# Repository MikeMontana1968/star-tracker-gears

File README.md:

# Sidereal star tracker

A standalone device that turns a camera at one revolution per **sidereal day**
(86164.0905 s) for wide-field astrophotography. It wakes at dusk, configures and
starts a GoPro HERO6 night lapse, tracks until dawn, stops the camera, and
rewinds ready for the next night.

---

> **Picking this up again?** Read **[RESUME.md](RESUME.md)** first. The
> controller PCB (Rev C, for the 30-pin ESP32 in hand) is generated, clean
> in ERC and DRC, and ready to order.
>
> **Building it?** The illustrated assembly guide is
> [docs/assembly_guide/stjarnspar.html](docs/assembly_guide/stjarnspar.html):
> gearbox, board, smoke test, wiring, first power-up, use, and the schematics.
> Rebuild it with `python docs/assembly_guide/build.py` (needs Fritzing 1.0.8
> and KiCad 10). The Fritzing wiring project is
> [hardware/fritzing/star_tracker_wiring.fzz](hardware/fritzing/star_tracker_wiring.fzz),
> generated by `gen_fritzing.py` from the KiCad layout.

## Where this stands

| Area | State |
|---|---|
| Gearbox design | **Settled.** 2048:1, verified in CAD, every STL manifold |
| Printer calibration | **Measured.** Post/hole offset 0.50 mm; motor pinion bore pending one test print |
| Backlash | **Validated** on a test pair at 0.25 mm. One drag spot traced to the pinion — reprint with Z Seam = Random |
| Baseplate | **Ordered** from SendCutSend, 4.3 mm 6061 |
| Output shaft + encoder | **Designed**, needs the bearing gauge printed before the tower |
| Electronics | **PCB Rev C** ([hardware/PCB.md](hardware/PCB.md)) — 150 x 100 mm, all through-hole, every module socketed, generated from source; laid out for the 30-pin ESP32 after the pin check. ERC/DRC clean, not yet fabricated |
| Firmware | **Architecture settled** ([FIRMWARE.md](FIRMWARE.md)); nothing written beyond the timing core |
| Under the sky | Not yet |

**Next three things**, in order:

1. Print `_scratch/BEARINGGAUGE_pockets.stl`, set `$BrgFit`, then print the tower.
2. Print `pinion.stl` + the two bore variants next to `stage.stl`; keep the one
   that slides onto the NEMA17 shaft without force.
3. Build the polar wedge. **Before** the gearbox — see §2 below.

---

## The train

```
NEMA17 --15T--> [120T|15T] --> [120T|15T] --> [120T|24T] --> 96T --> camera
   module 1.0       8:1            8:1            8:1        4:1
                                                        module 2.0
```

**8 × 8 × 8 × 4 = 2048 : 1**

| | |
|---|---|
| microsteps / sidereal day | 13,107,200 (200 steps × 1/32 × 2048) |
| step interval | 6573.80 µs |
| step rate | 152.13 steps/s |
| motor speed | 1.426 rpm |
| output resolution | 0.099 arcsec/µstep |
| centre distances | 67.5 / 67.5 / 67.5 / 120.0 mm |
| gear stack | 226.5 × 279 mm envelope, 24.5 mm tall |
| baseplate | 121.5 × 174 × 4.3 mm, ~182 g |

---

## The two things that actually matter

Everything else in this project falls out of these.

### 1. Only the final pinion's radius sets short-exposure trailing

For any mesh, both gears contribute equally to output error per unit
eccentricity — the pinion's smaller radius exactly cancels its higher reduction.
But their *periods* differ, and trailing depends on how much the error moves
**during** an exposure:

```
excursion over exposure t  =  (e / r_pinion) × 2π t / 86164
```

Only `r_pinion` survives. That one equation drove the redesign from 4608:1 to
2048:1: a module-2 24-tooth final pinion (r = 24 mm) instead of module-1 15-tooth
(r = 7.5 mm) cuts a 0.1 mm eccentricity from ~60 arcsec to ~19 arcsec on every
300 s sub. Stages 1–3 divide by 2048, 256 and 32 — they can be as sloppy as the
printer likes.

### 2. Polar alignment dominates all of it

```
1° of misalignment  →  ~16 arcsec/min of drift
```

That swamps every mechanical error above. A sight tube down the RA axis getting
you to 0.25° is worth more than any amount of gear precision. **Build the wedge
first.**

Derivations, rejected alternatives and the design history are in
**[DESIGN_NOTES.md](DESIGN_NOTES.md)**.

---

## Layout

Square fold, 90° at each stage. Shaft centres in mm:

| Shaft | x | y | Carries |
|---|---|---|---|
| 0 motor | 0 | 0 | 15T module-1 pinion |
| 1 | 67.5 | 0 | 120T + 15T |
| 2 | 67.5 | 67.5 | 120T + 15T |
| 3 | 0 | 67.5 | 120T + **24T module-2** |
| 4 output | 0 | −52.5 | 96T module-2, 196 mm OD, on bearings |

**Constraints this layout imposes** — all three were found by drawing it to scale:

- **Nothing over Ø13 mm inline at shafts 0–3.** Tightest radial clearance is
  `67.5 − 61 − 2.5 = 4.0 mm`, shaft to neighbouring wheel tip. A 625ZZ (16 mm)
  gives −1.5 mm and collides; a Ø10 spacer leaves 1.5 mm. **Never fit a stock
  5 mm shaft collar at shafts 2 or 3.**
- **Shafts 0 and 1 must stay below 19 mm.** The output wheel sits over both. A
  stock NEMA17 shaft is 24 mm and fouls it — trim to ~10 mm above the plate.
- **No top plate on shafts 0 and 1**, same reason. Cantilever them; their errors
  divide by 2048 and 256, so it costs nothing.

**Every mesh needs its own Z band.** `pinion_tip + wheel_tip = a + 2m` always, so
a pinion collides with any adjacent wheel, mating or not. Four meshes, four
bands, irreducible. Band *height* can shrink (3 mm faces take the stack from
24.5 to 16 mm) but band *count* cannot.

---

## Baseplate

121.5 × 174 × **4.3 mm** 6061 aluminium, ~182 g (4.3 was the nearest stock to
the 4.0 designed). Cut, not printed — too big for the bed, and it wants
stiffness rather than strength.

Thickness is dimensionally free here: **all gear heights reference the plate's
top face**, so it lives below the datum. It only moves fastener lengths.

The outline is a hull of lobes at the five shaft centres, **not** a slab under
the whole gear footprint: the wheels overhang on purpose, so the plate only
carries the shafts and the motor. That is what takes it from ~740 g to 170 g.

The wedge/tripod interface is **4 × M5 on Ø50 centred on the output axis**, not
on the plate centroid. The camera moment gets reacted where it is generated, and
that short load path is why 4 mm is enough.

- `out/docs/baseplate_cut.dxf` — **send this**, 4 ARC + 4 LINE + 16 CIRCLE.
  State **mm** on upload; R12 DXF has no reliable units record
- `out/docs/baseplate_cut.svg` — same geometry as SVG, 17 closed contours
- `out/docs/baseplate_template.pdf` — 1:1 on US Letter, two scale bars
- `out/docs/baseplate_assembly_guide.pdf` — bench reference: component outlines,
  spacer heights, fastener sizes. **Not to scale**, by necessity — the gear
  footprint is 226 × 279 mm

`baseplate_geom.py` is the single source for all three, so they cannot drift.
Never export DXF from OpenSCAD — it emits 708 loose LINE segments and no
circles at all.

---

## Output shaft and AS5600 encoder

The output is the one shaft that rotates. The encoder magnet must sit on the axis
and turn with the wheel, and the camera load wants real bearings anyway.

Printed tower halves, hubs, washer, cap and bracket, plus a 5 mm ground shaft
**cut to 55 mm**, 2 × 625ZZ, a **diametric** 6 × 2.5 magnet and an AS5600
breakout. Verified: **magnet face to die = 2.0 mm**, inside the sensor's
0.5–3.0 mm window; bearing centres 30 mm apart.

Three design points worth not undoing:

- **The tower halves clamp the baseplate between them** (Rev B). Rev A's cone
  under the flange sat inside the plate. See PRINTING.md.

- **The wheel locates on a Ø22 register** on the lower hub and is clamped by six
  M3 — not centred by its own bore. A printed 5.2 bore on a 5 mm shaft is worth
  ~0.2 mm of eccentricity, which is exactly what §1 says to avoid.
- **The sensor bracket registers on the same tower boss that holds the lower
  bearing, and stops against the tower's clamp disc.** The AS5600 needs the
  magnet centred within ~0.25 mm and gapped at 2.0 mm; both come from printed
  features rather than from careful assembly.

Firmware aid: the AS5600's `AGC` and `MAGNITUDE` registers report "too far / too
close" as a number, so the air gap is measured, not guessed.

---

## Scheduled operation

Full architecture, cycle diagram, BOM and pin map: **[HARDWARE.md](HARDWARE.md)**.

- **ESP32, not a Pi.** Unattended robustness: a flat battery mid-write corrupts
  an SD card, LittleFS comes back. Also ~0.6 W cheaper, ≈7 Wh a night.
- **GoPro over WiFi, not BLE.** The documented GoPro BLE API starts at HERO9 —
  the earlier HERO5 Bluetooth failure was expected, not a Pi problem. HERO6 uses
  the `gpControl` HTTP API at 10.5.5.9, woken by a magic packet.
- **Captive web UI on the ESP32's own AP.** No app, no pairing. One radio means
  one mode at a time, which keeps the state machine simple.
- **~43 Wh per night, 69% of it the camera.** Three nights unaided needs 130 Wh;
  a 6 Ah pack plus a 20 W panel is lighter and never runs out.

**Two cycle rules that are not obvious:** always approach the start angle from
the forward direction (rewind reverses ~750 arcsec of backlash, which otherwise
gets taken up as drift during your first subs), and bias the counterweight so the
mesh stays loaded on one flank.

### Why there is no speed feedback loop

A stepper is synchronous, and the ESP32 crystal is ±20 ppm — over a 300 s exposure
that is 0.000025° at the output. There is nothing for a speed loop to correct. Use
StallGuard for *stall detection*, which is a real failure mode.

What must be exact is the step interval: 6573.80 µs is not an integer, and
rounding costs ~5 s/day of drift. `sidereal_drive.ino` carries the remainder in a
64-bit accumulator, so the rate is exact for **any** ratio — which is what freed
the design to choose gears for mechanical convenience.

---

## Printer calibration — measured, not guessed

These live at the top of `build.ps1`. They are the hardest-won numbers here.

| Constant | Value | How it was found |
|---|---|---|
| `$Bore` | 6.00 | gears run on #12 screws (5.49 mm), was 5.20 for nails |
| `$MotorBore` | 5.45 | NEMA17's ground 5.00 mm shaft needs its own bore |
| `$PostD` | 4.70 | fit gauge |
| `$BrgFit` | 0.50 | **provisional** — print the bearing gauge |

**A printed post must run ~0.50 mm under a printed hole's nominal diameter** for
a snug rotating fit on this printer. That is hole shrink plus post growth
combined, and it is on the high side of typical (0.30–0.40), which hints flow
runs a few percent hot.

Three gauges exist because these cannot be predicted, only measured:
`FITGAUGE` (posts), `BOREGAUGE` (holes), `BEARINGGAUGE` (625ZZ pockets).

---

## Repo layout

```
star_tracker_gears.scad     the model — single source for every part
make_baseplate_pdf.py       1:1 drilling template (reportlab)
build.ps1                   regenerates every artifact
firmware/sidereal_drive/    ESP32 sketch
PRINTING.md                 what to print, in what order, with what settings
DESIGN_NOTES.md             why the gearbox is what it is
HARDWARE.md                 electronics architecture, BOM
FIRMWARE.md                 firmware architecture, pin map, build order — START HERE for code
hardware/                   the controller PCB, generated from Python
  PCB.md                    board design notes, jumpers, assembly order
  design.py                 netlist + values + the ESP32/TMC pin maps
  place.py                  floorplan; layout.py packer; route.py maze router
  star_tracker_ctrl/        the generated KiCad project
out/                        generated — meshes gitignored
  docs/                     renders, laser SVG, baseplate SVG, template
  _scratch/                 calibration gauges, test jig, superseded exports
```

## Building

```powershell
.\build.ps1                     # everything
.\build.ps1 -Group gears        # the parts you print
.\build.ps1 -Group encoder      # output shaft assembly
.\build.ps1 -Group calibration  # the three gauges
.\build.ps1 -Group docs         # renders, SVGs, PDF
.\build.ps1 -List               # show targets without building
```

Needs OpenSCAD 2021.01+ and Python with `reportlab`. Every STL target is checked
for `Simple: yes` and the build fails if one is not.

---

## Traps worth remembering

Each of these cost real time and none of them announce themselves.

- **OpenSCAD: `children()` nested inside `union()` inside `difference()` inside
  `if()` does not resolve.** The section cut silently did nothing. Apply cuts at
  the call site instead.
- **OpenSCAD preview mis-renders `difference()` when children carry `color()`.**
  Geometry was correct all along; only the OpenCSG preview lied. Section images
  need `--render`, which then discards colour — hence the exploded view.
- **PowerShell 5.1 strips inner quotes** from native-exe arguments, so
  `part="spacers"` arrives as a bare variable. Backslash-escape them. And `2>&1`
  on a native command wraps stderr in ErrorRecords that abort under
  `$ErrorActionPreference = 'Stop'`.
- **A part can be un-printable in every orientation.** The bearing tower had a
  166 mm2 first layer one way up and an 8 mm 90° ledge the other. Splitting it
  fixed the printing. Check bed contact area, not just overhang angle.
- **Check a printable part against its neighbours, not just the bed.** Rev A's
  split added a cone for printability that sat inside the aluminium plate. It
  was found by drawing the assembly guide, not by the build. Rev B puts the
  plate between the halves, so each prints plate-face-down and only narrows
  going up.
- **Verify meshes, not file sizes.** Bounding-box checks caught a wheel that had
  changed only in float formatting, and a D-shaft cut that had sliced the pinion
  into five disconnected bodies (`Volumes: 5` instead of 2).
- **Binaries need `.gitattributes`.** Without it a fresh Windows clone rewrites
  LF to CRLF *inside* the PDF and PNGs and corrupts them.

## Order of work

1. Calibration gauges, then the test pair. Tune `backlash`.
2. **Build the polar wedge before the gearbox.**
3. Open-loop drive, 50 mm lens, one 5-minute sub. **Measure the trailing.**
4. Only then decide what to fix. Adding an encoder before you have data is
   solving an imaginary problem — the encoder in this design is for *scheduling*
   and stall detection, not for correcting tracking.

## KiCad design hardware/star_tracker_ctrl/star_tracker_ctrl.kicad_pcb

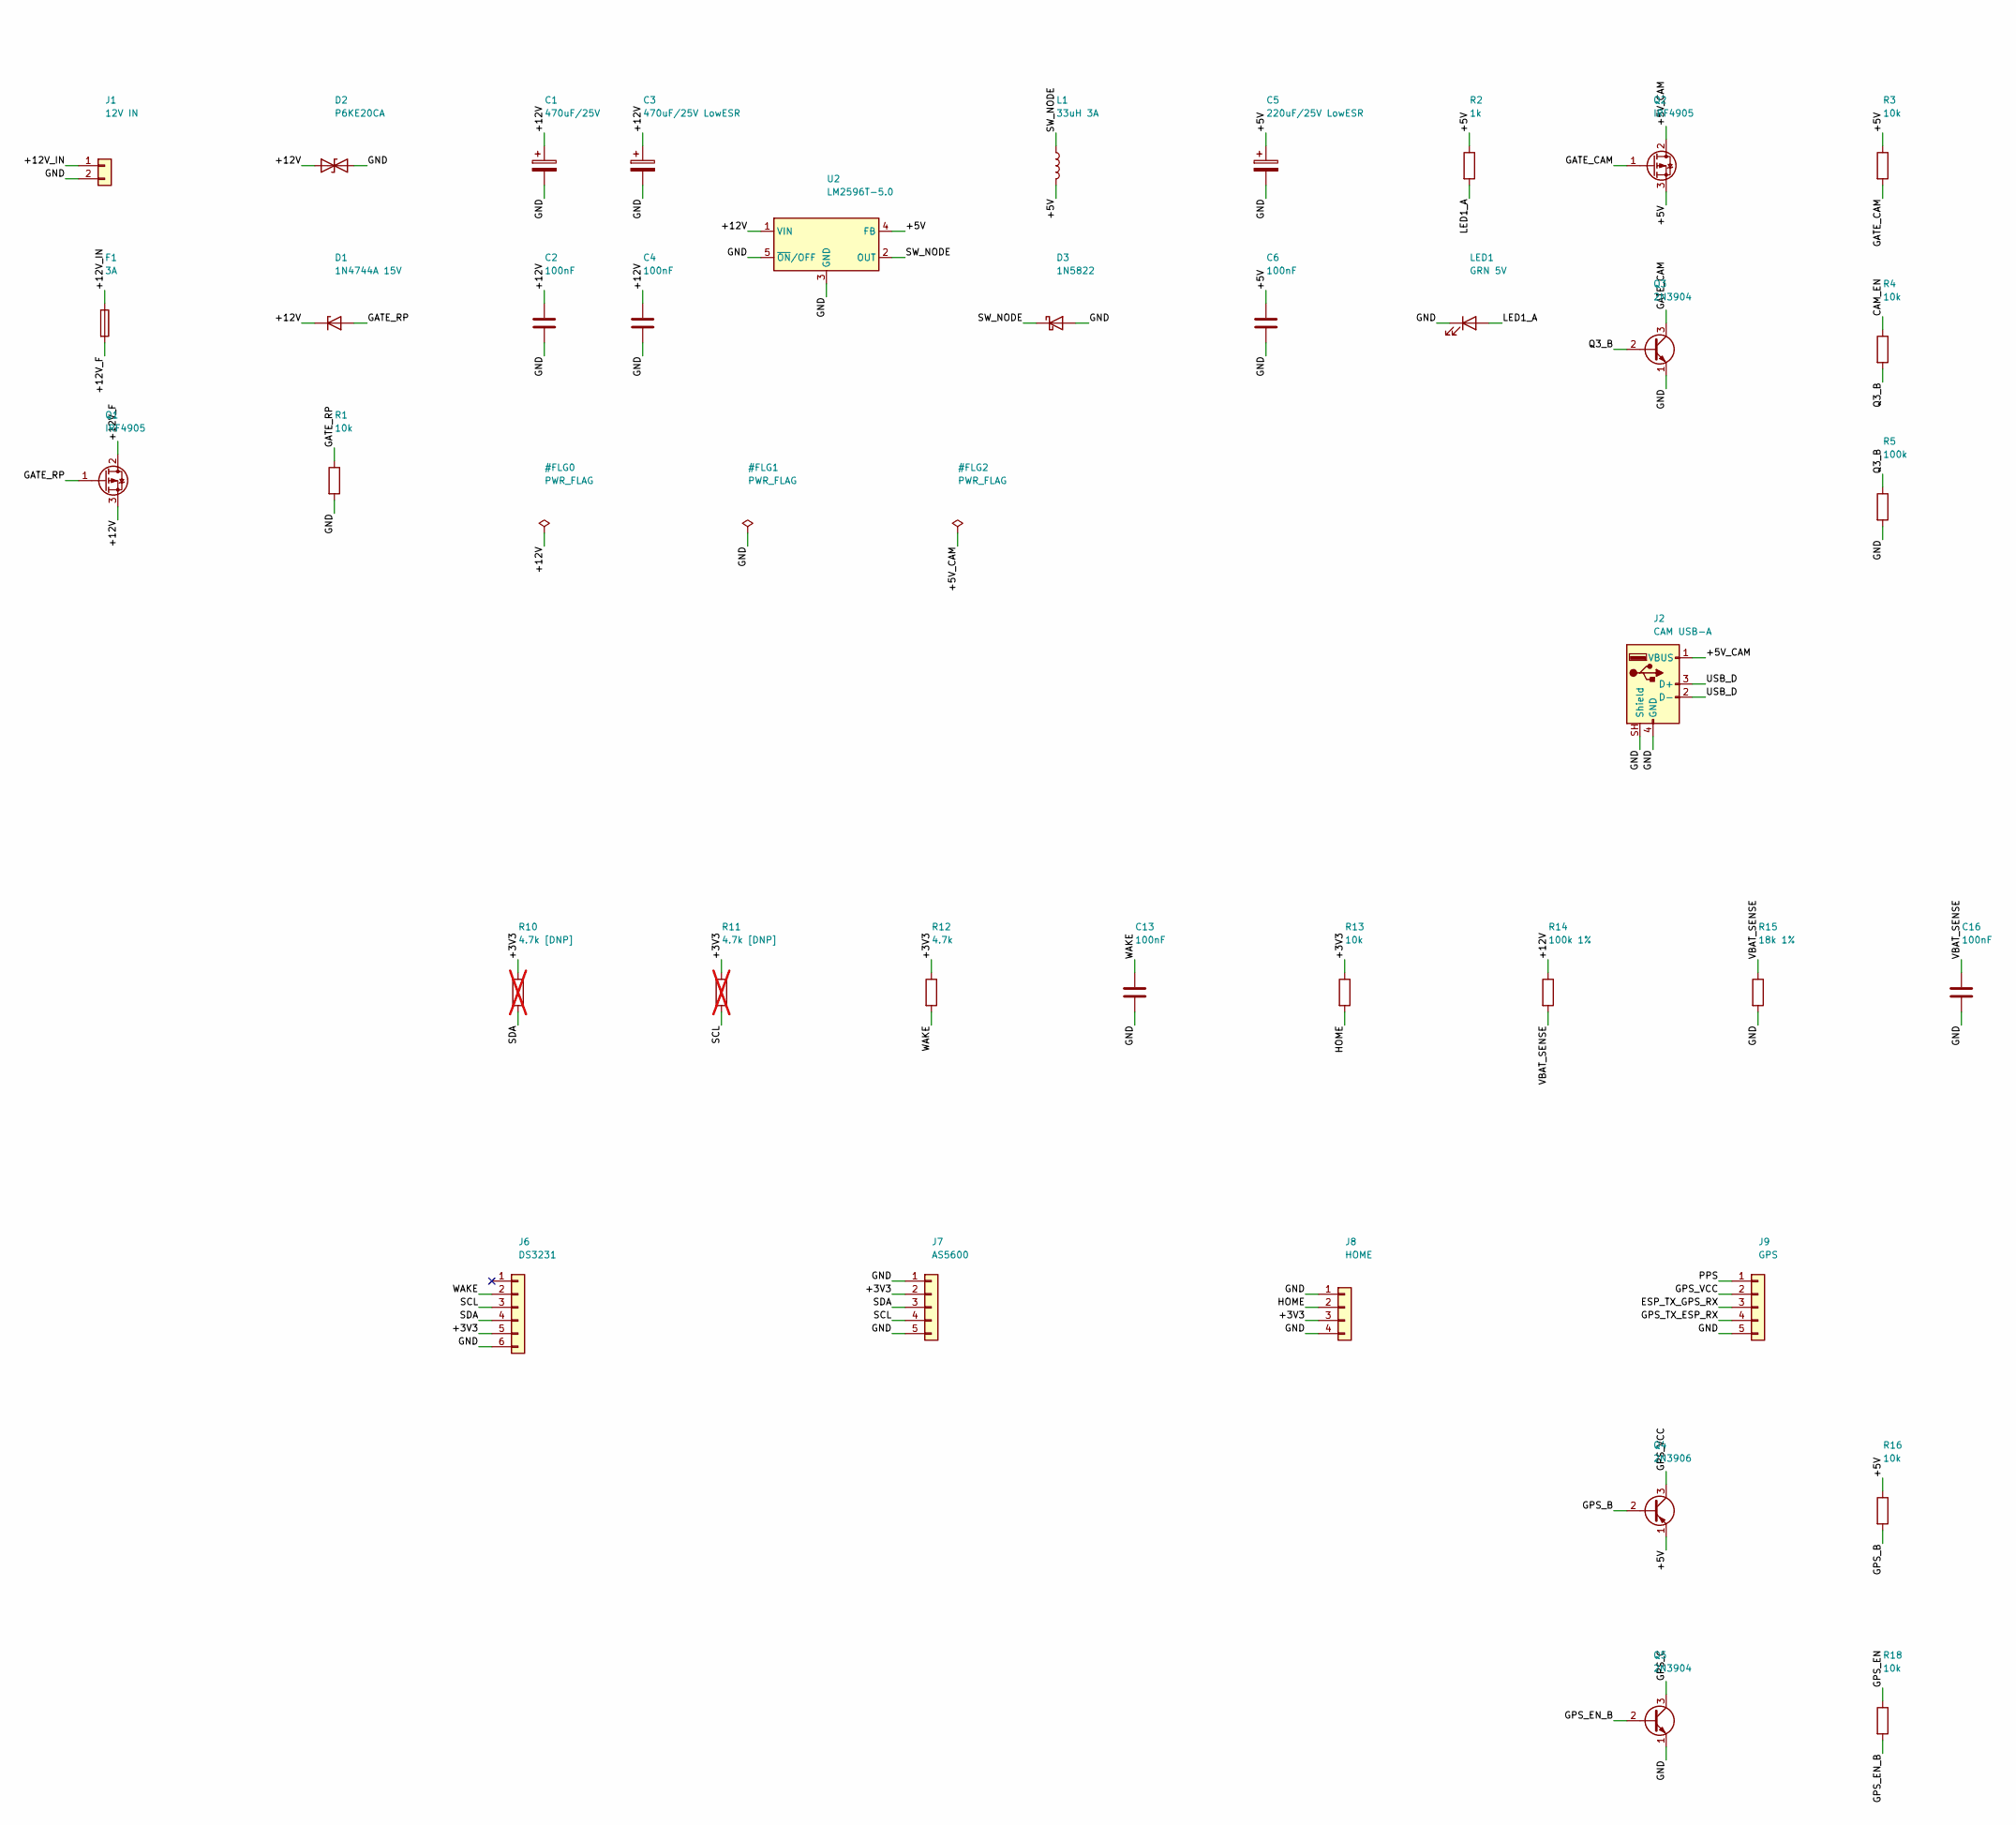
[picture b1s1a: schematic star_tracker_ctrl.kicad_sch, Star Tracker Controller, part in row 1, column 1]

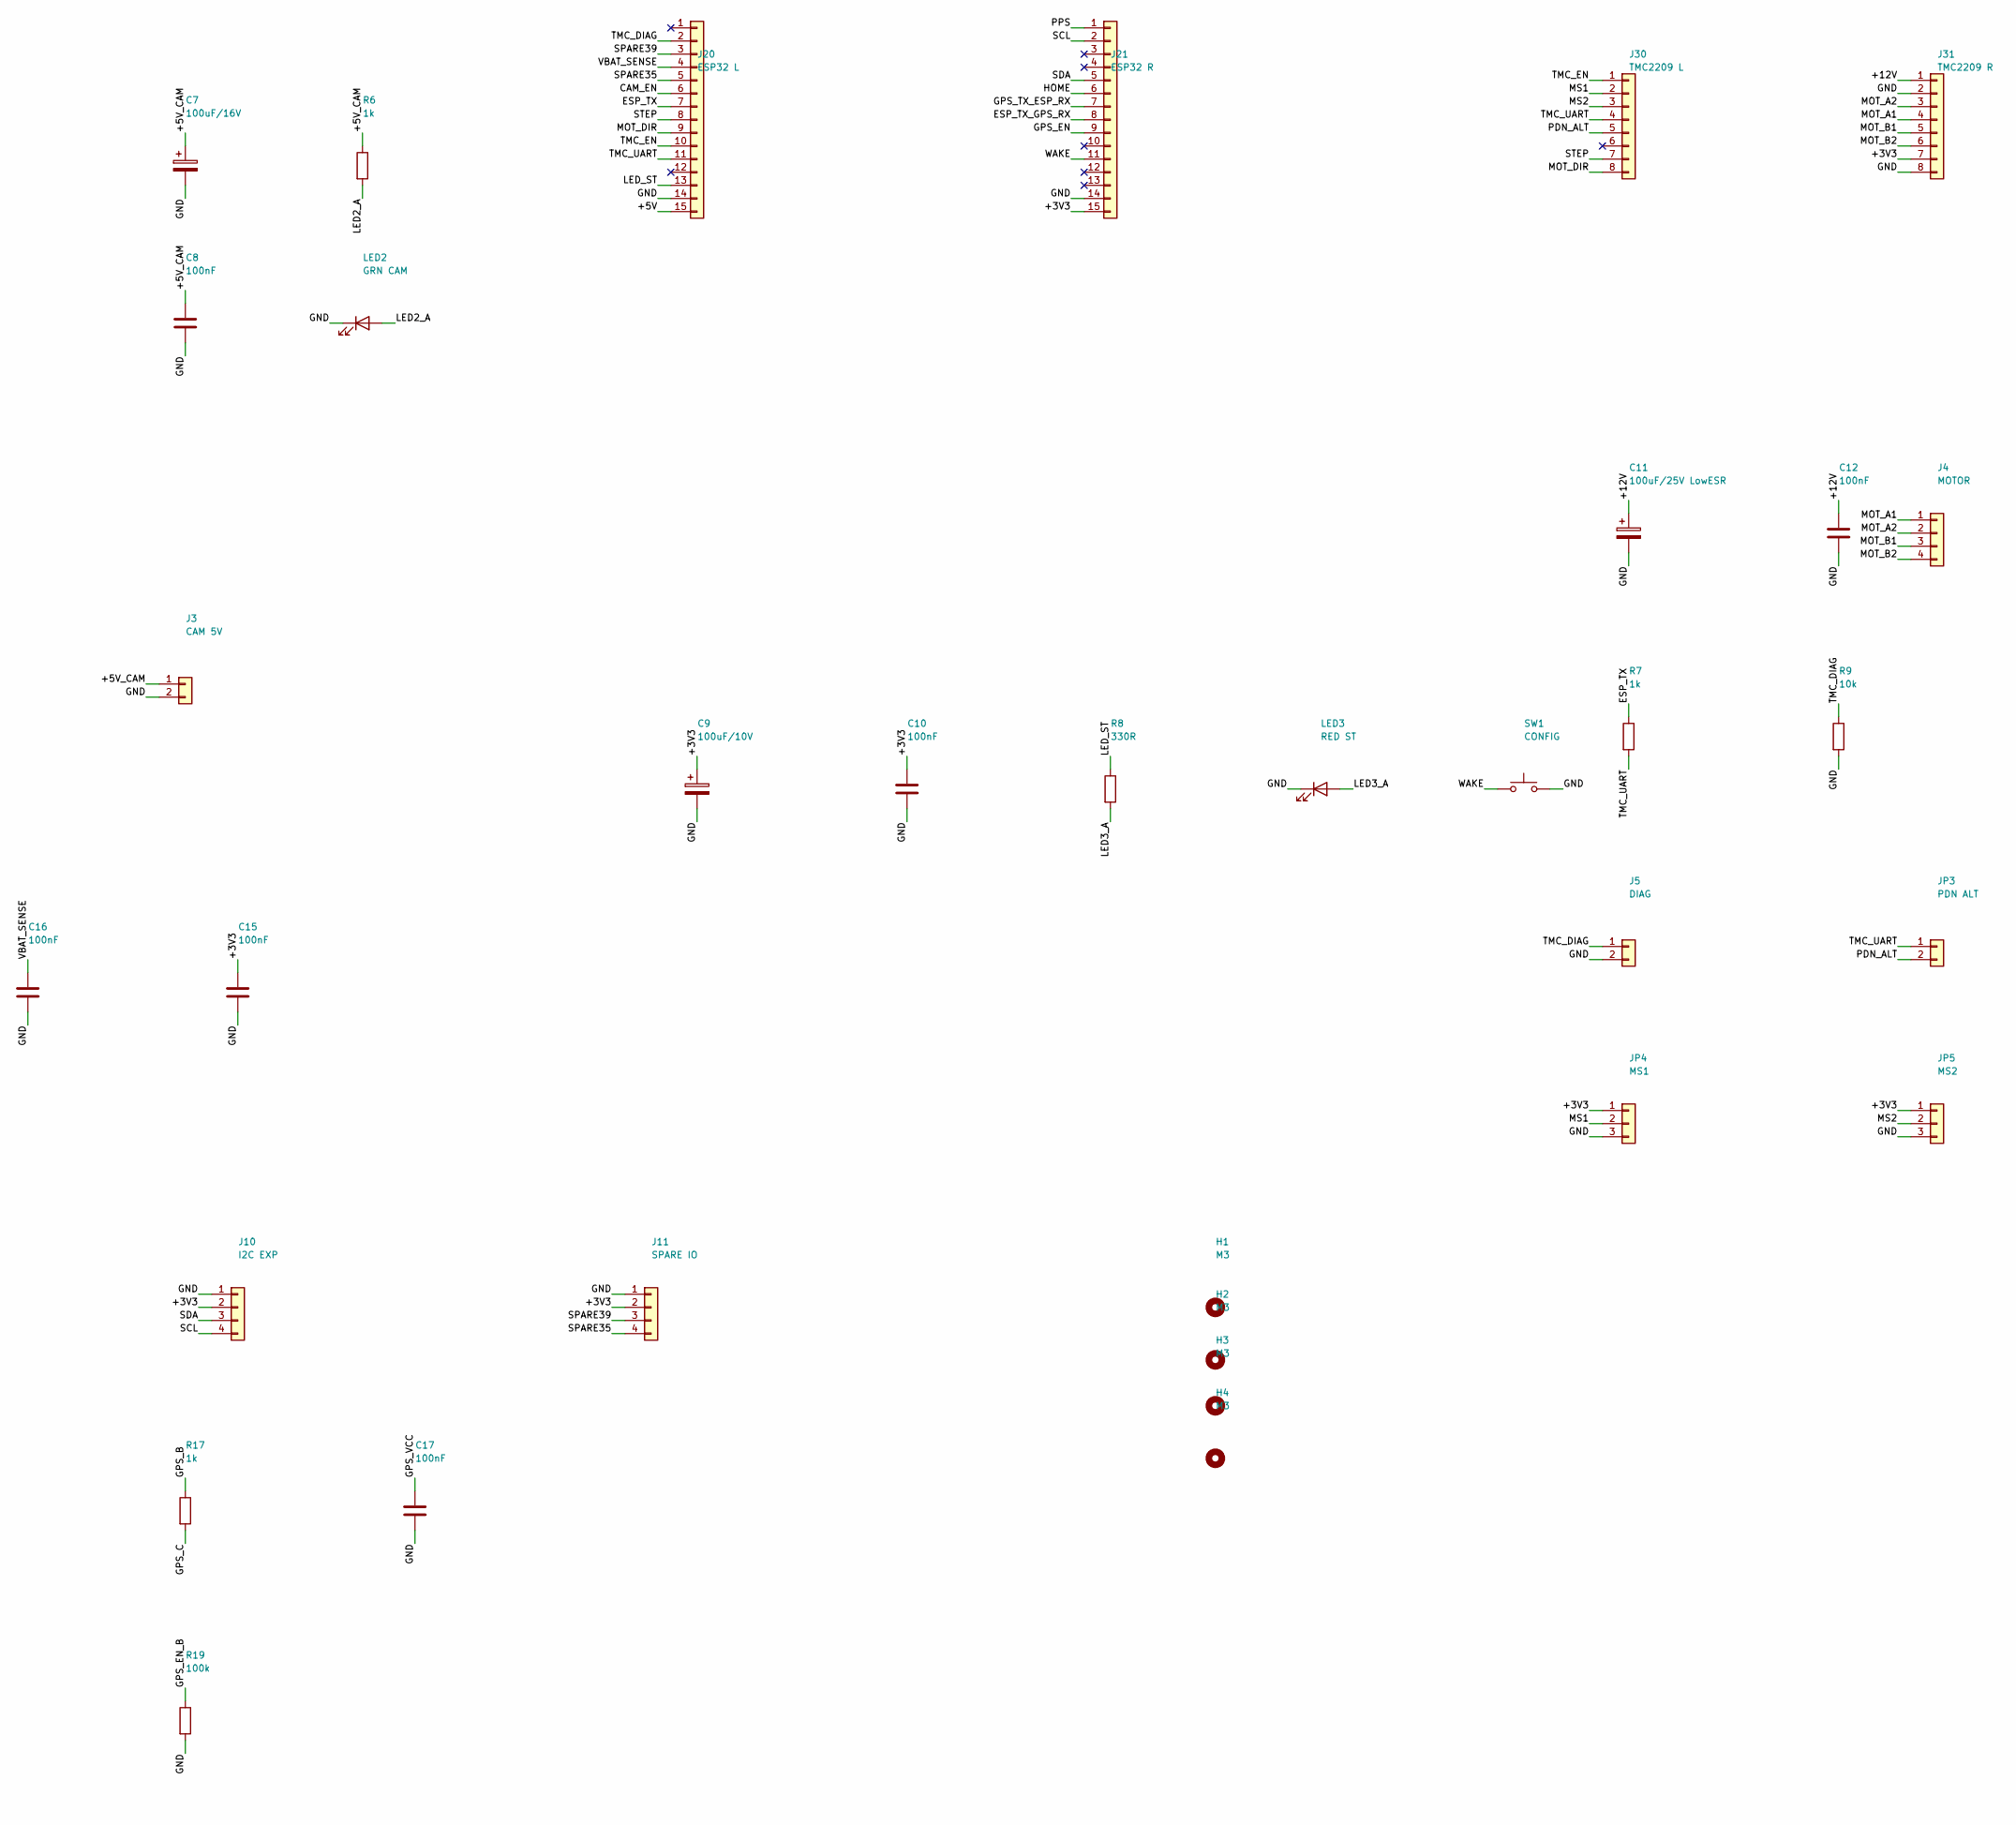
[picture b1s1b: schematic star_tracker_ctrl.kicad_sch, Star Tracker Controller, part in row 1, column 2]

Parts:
C1: 470uF/25V; CP_Radial_D10.0mm_P5.00mm
C2, C4, C6, C8, C10, C12, C13, C15, C16, C17: 100nF; C_Disc_D5.0mm_W2.5mm_P2.50mm
C3: 470uF/25V LowESR; CP_Radial_D10.0mm_P5.00mm
C5: 220uF/25V LowESR; CP_Radial_D10.0mm_P5.00mm
C7: 100uF/16V; CP_Radial_D8.0mm_P3.50mm
C9: 100uF/10V; CP_Radial_D8.0mm_P3.50mm
C11: 100uF/25V LowESR; CP_Radial_D10.0mm_P5.00mm
D1: 1N4744A 15V; D_DO-41_SOD81_P2.54mm_Vertical_CathodeUp
D2: P6KE20CA; D_DO-15_P3.81mm_Vertical_AnodeUp
D3: 1N5822; D_DO-201AD_P5.08mm_Vertical_CathodeUp
F1: 3A; Fuseholder_Clip-5x20mm_Littelfuse_111_Inline_P20.00x5.00mm_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
H1, H2, H3, H4: M3; MountingHole_3.2mm_M3
J1: 12V IN; TerminalBlock_MaiXu_MX126-5.0-02P_1x02_P5.00mm
J2: CAM USB-A; USB_A_Wuerth_614004134726_Horizontal
J3: CAM 5V; TerminalBlock_MaiXu_MX126-5.0-02P_1x02_P5.00mm
J4: MOTOR; TerminalBlock_MaiXu_MX126-5.0-04P_1x04_P5.00mm
J5: DIAG; PinHeader_1x02_P2.54mm_Vertical
J6: DS3231; PinSocket_1x06_P2.54mm_Vertical
J7: AS5600; PinHeader_1x05_P2.54mm_Vertical
J8: HOME; PinHeader_1x04_P2.54mm_Vertical
J9: GPS; PinHeader_1x05_P2.54mm_Vertical
J10: I2C EXP; PinHeader_1x04_P2.54mm_Vertical
J11: SPARE IO; PinHeader_1x04_P2.54mm_Vertical
J20: ESP32 L; PinSocket_1x15_P2.54mm_Vertical
J21: ESP32 R; PinSocket_1x15_P2.54mm_Vertical
J30: TMC2209 L; PinSocket_1x08_P2.54mm_Vertical
J31: TMC2209 R; PinSocket_1x08_P2.54mm_Vertical
JP3: PDN ALT; PinHeader_1x02_P2.54mm_Vertical
JP4: MS1; PinHeader_1x03_P2.54mm_Vertical
JP5: MS2; PinHeader_1x03_P2.54mm_Vertical
L1: 33uH 3A; L_Radial_D12.0mm_P5.00mm_Fastron_11P
LED1: GRN 5V; LED_D3.0mm
LED2: GRN CAM; LED_D3.0mm
LED3: RED ST; LED_D3.0mm
Q1, Q2: IRF4905; TO-220-3_Vertical
Q3, Q5: 2N3904; TO-92_Inline_Wide
Q4: 2N3906; TO-92_Inline_Wide
R1, R3, R4, R9, R13, R16, R18: 10k; R_Axial_DIN0207_L6.3mm_D2.5mm_P2.54mm_Vertical
R2, R6, R7, R17: 1k; R_Axial_DIN0207_L6.3mm_D2.5mm_P2.54mm_Vertical
R5, R19: 100k; R_Axial_DIN0207_L6.3mm_D2.5mm_P2.54mm_Vertical
R8: 330R; R_Axial_DIN0207_L6.3mm_D2.5mm_P2.54mm_Vertical
R10, R11: 4.7k [DNP]; R_Axial_DIN0207_L6.3mm_D2.5mm_P2.54mm_Vertical; not fitted
R12: 4.7k; R_Axial_DIN0207_L6.3mm_D2.5mm_P2.54mm_Vertical
R14: 100k 1%; R_Axial_DIN0207_L6.3mm_D2.5mm_P2.54mm_Vertical
R15: 18k 1%; R_Axial_DIN0207_L6.3mm_D2.5mm_P2.54mm_Vertical
SW1: CONFIG; SW_PUSH_6mm
U2: LM2596T-5.0; TO-220-5_P3.4x3.7mm_StaggerOdd_Lead3.8mm_Vertical

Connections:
+3V3: C9.1, C10.1, C15.1, J6.5, J7.2, J8.3, J10.2, J11.2, J21.15, J31.7, JP4.1, JP5.1, R10.1, R11.1, R12.1, R13.1
+5V: C5.1, C6.1, J20.15, L1.2, Q2.3 (S), Q4.1 (E), R2.1, R3.1, R16.1, U2.4 (FB)
+5V_CAM: C7.1, C8.1, J2.1 (VBUS), J3.1, Q2.2 (D), R6.1
+12V: C1.1, C2.1, C3.1, C4.1, C11.1, C12.1, D1.1 (K), D2.1 (A1), J31.1, Q1.3 (S), R14.1, U2.1 (VIN)
+12V_F: F1.2, Q1.2 (D)
+12V_IN: F1.1, J1.1
CAM_EN: J20.6, R4.1
ESP_TX: J20.7, R7.1
ESP_TX_GPS_RX: J9.3, J21.8
GATE_CAM: Q2.1 (G), Q3.3 (C), R3.2
GATE_RP: D1.2 (A), Q1.1 (G), R1.1
GND: C1.2, C2.2, C3.2, C4.2, C5.2, C6.2, C7.2, C8.2, C9.2, C10.2, C11.2, C12.2, C13.2, C15.2, C16.2, C17.2, D2.2 (A2), D3.2 (A), J1.2, J2.4 (GND), J2.SH (Shield), J3.2, J5.2, J6.6, J7.1, J7.5, J8.1, J8.4, J9.5, J10.1, J11.1, J20.14, J21.14, J31.2, J31.8, JP4.3, JP5.3, LED1.1 (K), LED2.1 (K), LED3.1 (K), Q3.1 (E), Q5.1 (E), R1.2, R5.2, R9.2, R15.2, R19.2, SW1.2, U2.3 (GND), U2.5 (~ON/OFF)
GPS_B: Q4.2 (B), R16.2, R17.1
GPS_C: Q5.3 (C), R17.2
GPS_EN: J21.9, R18.1
GPS_EN_B: Q5.2 (B), R18.2, R19.1
GPS_TX_ESP_RX: J9.4, J21.7
GPS_VCC: C17.1, J9.2, Q4.3 (C)
HOME: J8.2, J21.6, R13.2
LED1_A: LED1.2 (A), R2.2
LED2_A: LED2.2 (A), R6.2
LED3_A: LED3.2 (A), R8.2
LED_ST: J20.13, R8.1
MOT_A1: J4.1, J31.4
MOT_A2: J4.2, J31.3
MOT_B1: J4.3, J31.5
MOT_B2: J4.4, J31.6
MOT_DIR: J20.9, J30.8
MS1: J30.2, JP4.2
MS2: J30.3, JP5.2
PDN_ALT: J30.5, JP3.2
PPS: J9.1, J21.1
Q3_B: Q3.2 (B), R4.2, R5.1
SCL: J6.3, J7.4, J10.4, J21.2, R11.2
SDA: J6.4, J7.3, J10.3, J21.5, R10.2
SPARE35: J11.4, J20.5
SPARE39: J11.3, J20.3
STEP: J20.8, J30.7
SW_NODE: D3.1 (K), L1.1, U2.2 (OUT)
TMC_DIAG: J5.1, J20.2, R9.1
TMC_EN: J20.10, J30.1
TMC_UART: J20.11, J30.4, JP3.1, R7.2
USB_D: J2.2 (D-), J2.3 (D+)
VBAT_SENSE: C16.1, J20.4, R14.2, R15.1
WAKE: C13.1, J6.2, J21.11, R12.2, SW1.1

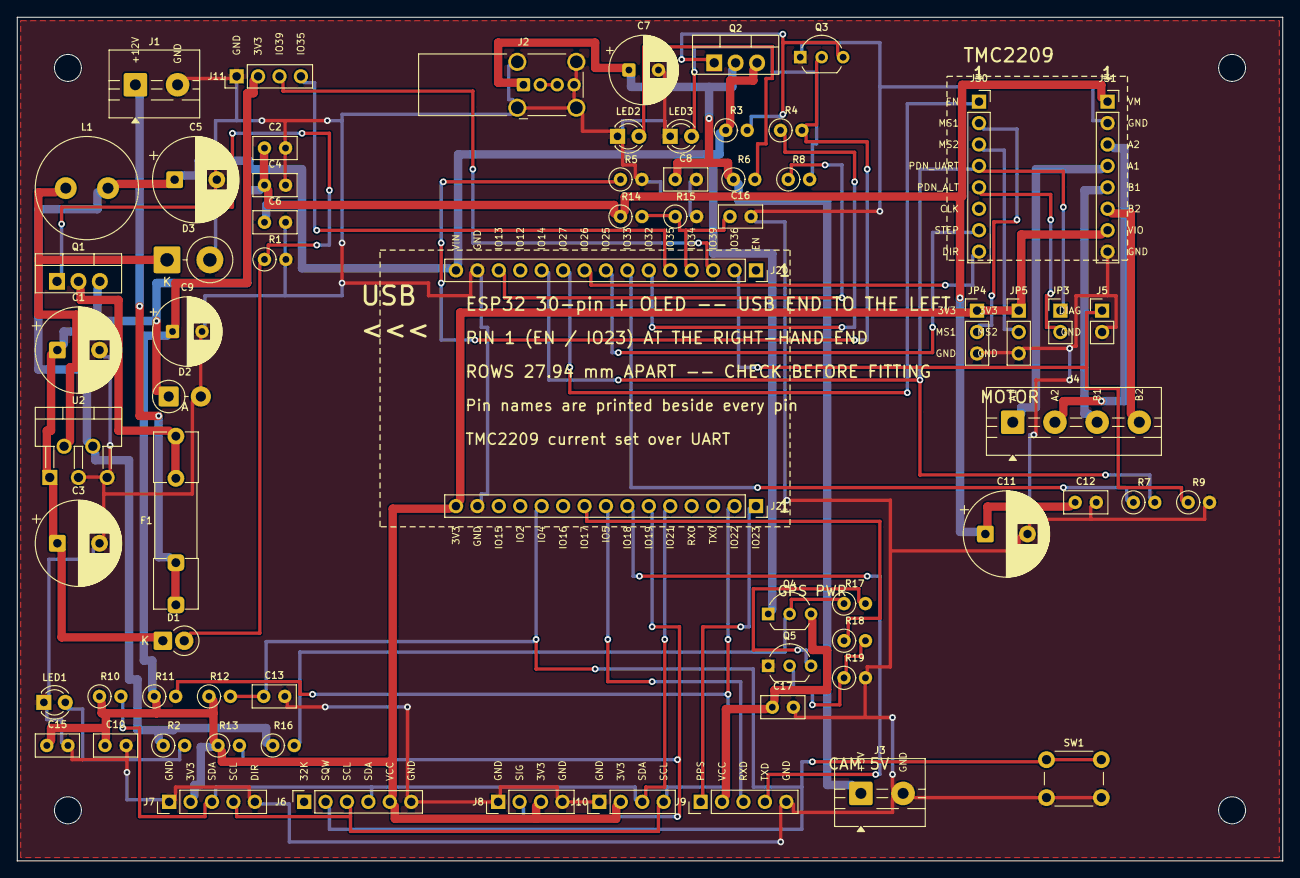
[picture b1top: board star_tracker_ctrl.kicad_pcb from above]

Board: 2 copper layers, 150.0 x 100.0 mm, 72 parts (0 on the bottom side), 45 nets.

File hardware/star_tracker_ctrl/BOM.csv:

Qty,Refs,Value,Footprint,Fitted,Note
1,"C1","470uF/25V","CP_Radial_D10.0mm_P5.00mm",yes,""
1,"C11","100uF/25V LowESR","CP_Radial_D10.0mm_P5.00mm",yes,"VMOT bulk - MUST sit at the driver socket"
10,"C10 C12 C13 C15 C16 C17 C2 C4 C6 C8","100nF","C_Disc_D5.0mm_W2.5mm_P2.50mm",yes,""
1,"C3","470uF/25V LowESR","CP_Radial_D10.0mm_P5.00mm",yes,""
1,"C5","220uF/25V LowESR","CP_Radial_D10.0mm_P5.00mm",yes,""
1,"C7","100uF/16V","CP_Radial_D8.0mm_P3.50mm",yes,""
1,"C9","100uF/10V","CP_Radial_D8.0mm_P3.50mm",yes,""
1,"D1","1N4744A 15V","D_DO-41_SOD81_P2.54mm_Vertical_CathodeUp",yes,"Vgs clamp, cathode to source"
1,"D2","P6KE20CA","D_DO-15_P3.81mm_Vertical_AnodeUp",yes,""
1,"D3","1N5822","D_DO-201AD_P5.08mm_Vertical_CathodeUp",yes,"catch diode, cathode to SW node"
1,"F1","3A","Fuseholder_Clip-5x20mm_Littelfuse_111_Inline_P20.00x5.00mm_D1.05mm_Horizontal",yes,""
1,"J1","12V IN","TerminalBlock_MaiXu_MX126-5.0-02P_1x02_P5.00mm",yes,"12-14.6V LiFePO4 in"
1,"J10","I2C EXP","PinHeader_1x04_P2.54mm_Vertical",yes,"v2 compass"
1,"J11","SPARE IO","PinHeader_1x04_P2.54mm_Vertical",yes,"the upper row's two free pins; both input-only"
1,"J2","CAM USB-A","USB_A_Wuerth_614004134726_Horizontal",yes,"D+/D- shorted = dedicated charging port"
1,"J20","ESP32 L","PinSocket_1x15_P2.54mm_Vertical",yes,""
1,"J21","ESP32 R","PinSocket_1x15_P2.54mm_Vertical",yes,""
1,"J3","CAM 5V","TerminalBlock_MaiXu_MX126-5.0-02P_1x02_P5.00mm",yes,""
1,"J30","TMC2209 L","PinSocket_1x08_P2.54mm_Vertical",yes,""
1,"J31","TMC2209 R","PinSocket_1x08_P2.54mm_Vertical",yes,""
1,"J4","MOTOR","TerminalBlock_MaiXu_MX126-5.0-04P_1x04_P5.00mm",yes,"pins 1-2 one coil, 3-4 the other"
1,"J5","DIAG","PinHeader_1x02_P2.54mm_Vertical",yes,""
1,"J6","DS3231","PinSocket_1x06_P2.54mm_Vertical",yes,"ZS-042 order: 32K SQW SCL SDA VCC GND"
1,"J7","AS5600","PinHeader_1x05_P2.54mm_Vertical",yes,"remote on the encoder bracket; pin5 = DIR->GND"
1,"J8","HOME","PinHeader_1x04_P2.54mm_Vertical",yes,"optional opto flag; GND on BOTH end pins so the pour can always reach one of them"
1,"J9","GPS","PinHeader_1x05_P2.54mm_Vertical",yes,"GY-NEO6MV2: pins 2-5 match its VCC/RX/TX/GND cable; PPS is a flying lead from the module's PPS LED pad"
1,"JP3","PDN ALT","PinHeader_1x02_P2.54mm_Vertical",yes,""
1,"JP4","MS1","PinHeader_1x03_P2.54mm_Vertical",yes,""
1,"JP5","MS2","PinHeader_1x03_P2.54mm_Vertical",yes,""
1,"L1","33uH 3A","L_Radial_D12.0mm_P5.00mm_Fastron_11P",yes,""
1,"LED1","GRN 5V","LED_D3.0mm",yes,""
1,"LED2","GRN CAM","LED_D3.0mm",yes,""
1,"LED3","RED ST","LED_D3.0mm",yes,""
2,"Q1 Q2","IRF4905","TO-220-3_Vertical",yes,"reverse-polarity; drain to source of supply"
2,"Q3 Q5","2N3904","TO-92_Inline_Wide",yes,""
1,"Q4","2N3906","TO-92_Inline_Wide",yes,"PNP high-side switch; the module's own LDO makes 3.3V from this"
7,"R1 R13 R16 R18 R3 R4 R9","10k","R_Axial_DIN0207_L6.3mm_D2.5mm_P2.54mm_Vertical",yes,""
2,"R10 R11","4.7k","R_Axial_DIN0207_L6.3mm_D2.5mm_P2.54mm_Vertical",NO,"omit if the DS3231 module already has pull-ups (most do)"
1,"R12","4.7k","R_Axial_DIN0207_L6.3mm_D2.5mm_P2.54mm_Vertical",yes,"the wired-OR pull-up; always populate"
1,"R14","100k 1%","R_Axial_DIN0207_L6.3mm_D2.5mm_P2.54mm_Vertical",yes,""
1,"R15","18k 1%","R_Axial_DIN0207_L6.3mm_D2.5mm_P2.54mm_Vertical",yes,"14.6V -> 2.23V at GPIO34"
4,"R17 R2 R6 R7","1k","R_Axial_DIN0207_L6.3mm_D2.5mm_P2.54mm_Vertical",yes,""
2,"R19 R5","100k","R_Axial_DIN0207_L6.3mm_D2.5mm_P2.54mm_Vertical",yes,"holds camera off while GPIO floats"
1,"R8","330R","R_Axial_DIN0207_L6.3mm_D2.5mm_P2.54mm_Vertical",yes,""
1,"SW1","CONFIG","SW_PUSH_6mm",yes,"also wakes from deep sleep via the GPIO4 wired-OR"
1,"U2","LM2596T-5.0","TO-220-5_P3.4x3.7mm_StaggerOdd_Lead3.8mm_Vertical",yes,"TO-220-5; needs a clip heatsink above ~1.5A"

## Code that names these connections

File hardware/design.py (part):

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# column the LOWER row (see place.py). Through-hole pin rows cannot be
# crossed, so: everything serving the driver, camera, divider and status LED
# sits on the upper row; everything bound for the bottom connector strip
# (I2C, RTC, encoder, GPS, home, wake) on the lower row. GPIO 2 is avoided --
# it must be low to enter download mode, and a pull-up there breaks flashing.
ESP32_LEFT = [
    ("EN",     "-"),
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    # read from the wrong end. Rev B named them GPS_TX / GPS_RX and wired the
    # ESP32's TX to the module's TXD -- TX to TX.
    ("IO18",   "GPS_TX_ESP_RX"),  # ESP32 receives
    ("IO5",    "ESP_TX_GPS_RX"),  # ESP32 transmits; strapping pin, idles high as TX
    ("IO17",   "GPS_EN"),     # drives Q5 -> Q4; GPS off while it floats at boot
    ("IO16",   "-"),          # free
    ("IO4",    "WAKE"),       # DS3231 INT + button, wired-OR; RTC-capable
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part("J9", "GPS", "Connector_Generic:Conn_01x05", hdr(5),
     {"1": "PPS", "2": "GPS_VCC", "3": "ESP_TX_GPS_RX", "4": "GPS_TX_ESP_RX", "5": "GND"},
     (82, 71, 90), (350, 260),
     note="GY-NEO6MV2: pins 2-5 match its VCC/RX/TX/GND cable; PPS is a "
          "flying lead from the module's PPS LED pad",
     labels=["PPS", "VCC", "RXD", "TXD", "GND"])
part("J10", "I2C EXP", "Connector_Generic:Conn_01x04", hdr(4),
     {"1": "GND", "2": "+3V3", "3": "SDA", "4": "SCL"},     (96, 71, 90), (430, 260), note="v2 compass",
     labels=["GND", "3V3", "SDA", "SCL"])
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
